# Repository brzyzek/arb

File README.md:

# arb
An arbitrary waveform generator.

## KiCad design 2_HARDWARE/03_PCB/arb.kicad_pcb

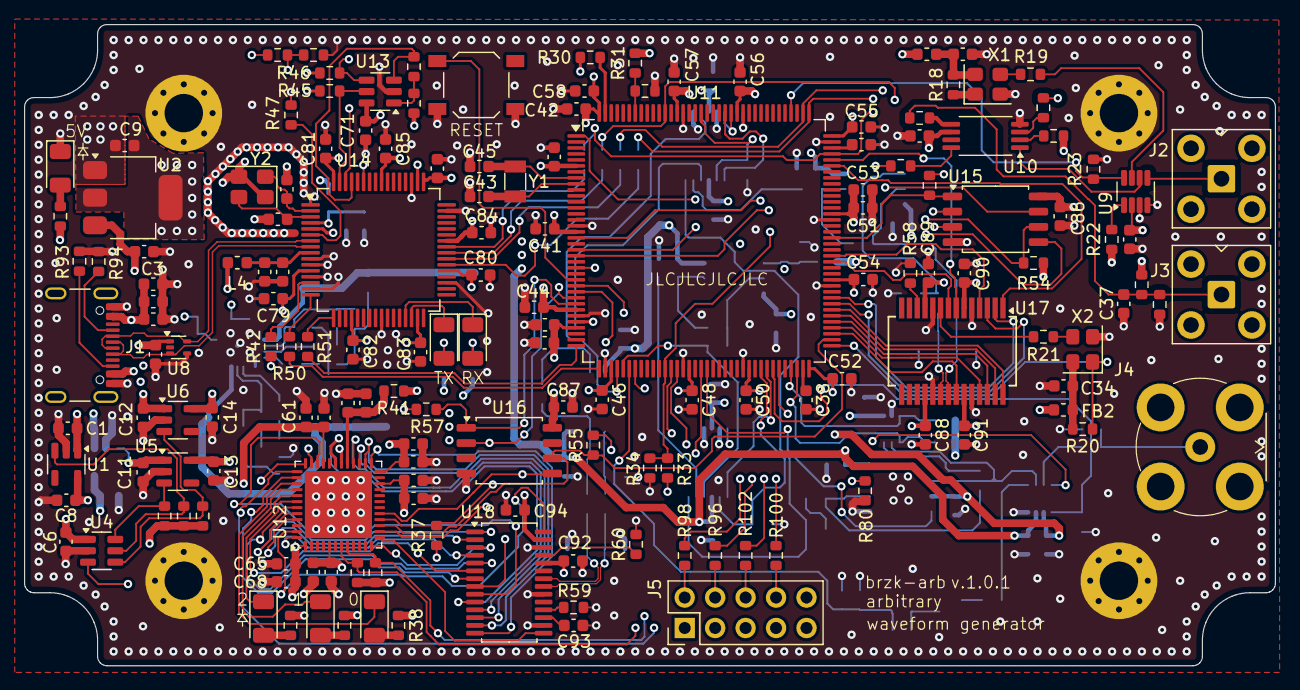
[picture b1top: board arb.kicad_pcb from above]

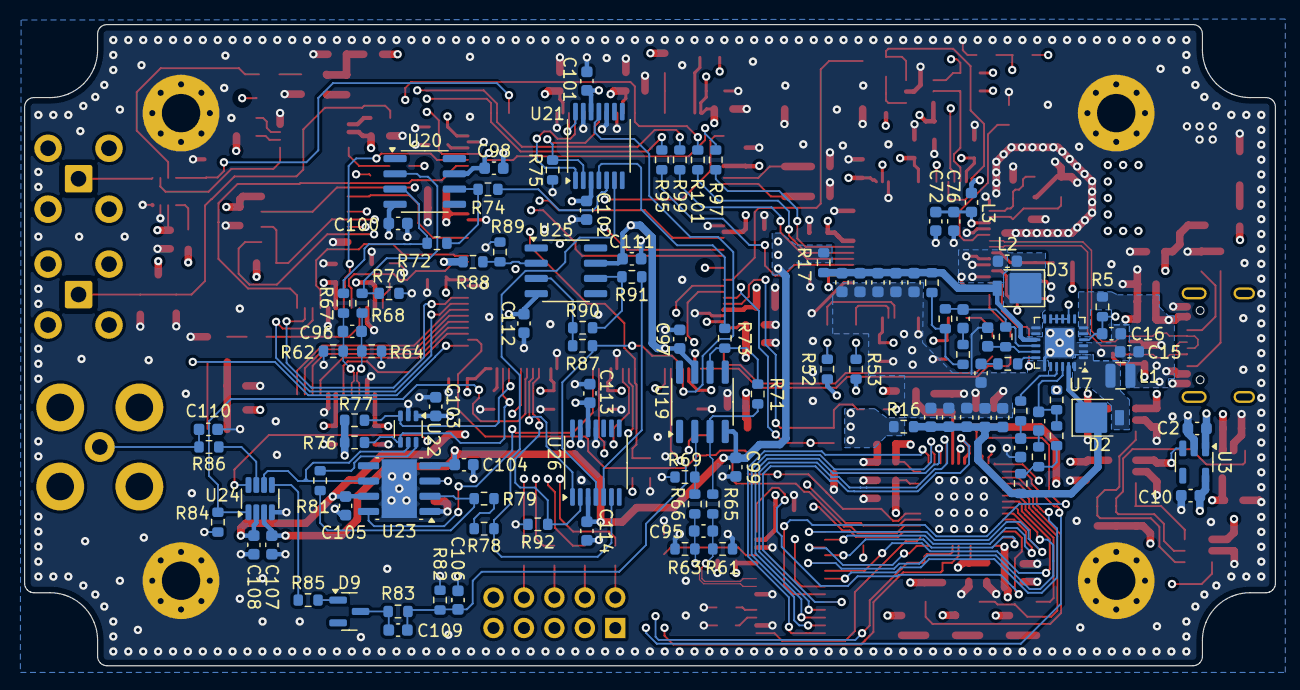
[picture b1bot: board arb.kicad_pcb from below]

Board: 6 copper layers, 104.3 x 53.5 mm, 271 parts (107 on the bottom side), 184 nets.

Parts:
C1, C2, C3, C7, C11, C12, C49, C53: 1u; C_0603_1608Metric
C4, C42: 10u; C_0603_1608Metric
C5, C15, C22, C23, C24, C25, C26, C27, C29, C30, C61, C62, C63, C68, C69, C70, C72, C74: 4.7u; C_0603_1608Metric
C6, C16, C28, C31, C32, C33, C34, C35, C36, C40, C41, C44, C46, C47, C48, C50, C51, C52, C54, C55, C56, C57, C58, C59, C60, C64, C65, C66, C67, C71, C76, C78, C79, C80, C81, C82, C83, C84, C85, C86, C87, C88, C89, C90, C91, C92, C93, C94, C97, C98, C99, C100, C101, C102, C103, C104, C105, C107, C108, C111, C112, C113, C114: 100n; C_0603_1608Metric
C8, C9, C10, C13, C14, C38, C39: 2.2u; C_0603_1608Metric
C17: 10n; C_0603_1608Metric
C18: 4.7n; C_0603_1608Metric
C19, C21: 6.8p; C_0603_1608Metric
C20: 220n; C_0603_1608Metric
C37, C95, C96, C106, C109: 5p; C_0603_1608Metric
C43, C45: 15p; C_0603_1608Metric
C73, C75: 27p; C_0603_1608Metric
C77: 3.3u; C_0603_1608Metric
C110: 22p; C_0603_1608Metric
D1, D4, D5, D6, D7, D8: LED; LED_1206_3216Metric
D2, D3: MBRM120ET1G; D_SMP_DO-216AA
D9: BAT54L; SOT-23
FB1: 100@100MHz; L_0603_1608Metric
FB2: 30@100MHz; L_0603_1608Metric
H1, H2, H3, H4: MOUNTING HOLE; MountingHole_3.2mm_M3_Pad_Via
J1: TYPE-C-31-M-12; USB_C_Receptacle_GCT_USB4105-xx-A_16P_TopMnt_Horizontal
J2, J3: SMA; SMA_TH_Horizontal_KH-SMA-K513-G
J4: BNC; BNC_TH_Horizontal_DOSIN-801-0050
J5: PH-00244; PinHeader_2x05_P2.54mm_Vertical
L1: 4.7u; L_SMD_L2.5_W2.0_Metric
L2: 4.7u; L_0603_1608Metric
L3, L4: 10u; L_0603_1608Metric
R1, R2, R3, R18, R20, R22, R23, R24, R30, R31, R32, R33, R34, R35, R36, R37, R43, R45, R46, R49, R54, R55, R56, R57, R60, R75, R84, R92: 10k; R_0603_1608Metric
R4, R69, R71, R87, R88, R89, R90: 499; R_0603_1608Metric
R5, R25, R26, R41: 100; R_0603_1608Metric
R6, R7, R10, R11, R14, R15, R16, R17, R29, R50, R51, R73, R74, R78, R79, R80, R81, R82, R85, R91, R95, R96, R97, R98, R99, R100, R101, R102: 0; R_0603_1608Metric
R8: 976k; R_0603_1608Metric
R9: 84.5k; R_0603_1608Metric
R12: 104k; R_0603_1608Metric
R13: 1.30M; R_0603_1608Metric
R19, R21, R27, R28, R61, R62, R63, R64: 24.9; R_0603_1608Metric
R38, R39, R40, R52, R53: 220; R_0603_1608Metric
R42, R70, R72: 1k; R_0603_1608Metric
R44: 2.05k; R_0603_1608Metric
R47: 12k; R_0603_1608Metric
R48, R76, R77: 4.7k; R_0603_1608Metric
R58: 3.9k; R_0603_1608Metric
R59: 2k; R_0603_1608Metric
R65, R66, R67, R68: 226; R_0603_1608Metric
R83: 124k; R_0603_1608Metric
R86: 50; R_0603_1608Metric
R93, R94: 5.1k; R_0603_1608Metric
SW1: TS-1187A-B-A-B; SW_SPST_BUTTON_TS-1187A-B-A-B
U1, U3: TLV70333DBV; SOT-23-5
U2: TLV76133DCY; SOT-223-3_TabPin2
U4: LM3880MF-1AA; SOT-23-6
U5: TLV70312DBV; SOT-23-5
U6: TLV70325DBV; SOT-23-5
U7: TPS65131RGE; VQFN-24-1EP_4x4mm_P0.5mm_EP2.45x2.45mm
U8: TPD2E001DRL; SOT-553
U9, U24: ADG1219BRJZ; SOT-23-8
U10: LMK1C1103PWR; TSSOP-8_4.4x3mm_P0.65mm
U11: STM32F446ZETx; LQFP-144_20x20mm_P0.5mm
U12: ICE40UP5K-SG48ITR; QFN-48-1EP_7x7mm_P0.5mm_EP5.6x5.6mm
U13: 93LC56BT-I_OT; SOT-23-6
U14: FT2232HL; LQFP-64_10x10mm_P0.5mm
U15, U16: W25Q128JVSIQ; SOIC-8_5.3x5.3mm_P1.27mm
U17: AD9850; SSOP-28_5.3x10.2mm_P0.65mm
U18: AD9744; TSSOP-28_4.4x9.7mm_P0.65mm
U19, U20, U25: LM6171; SOIC-8_3.9x4.9mm_P1.27mm
U21, U26: TMUX6104; TSSOP-14_4.4x5mm_P0.65mm
U22: TPL0401B-10; Texas_R-PDSO-G6
U23: THS3491; Texas_R-PDSO-G8_EP2.95x4.9mm_Mask2.4x3.1mm
X1: ASE-10.000MHz; Oscillator_SMD_Abracon_ASE-4Pin_3.2x2.5mm
X2: ASE-100.000MHz; Oscillator_SMD_Abracon_ASE-4Pin_3.2x2.5mm
Y1: 32.768k; Crystal_SMD_3215-2Pin_3.2x1.5mm
Y2: 12 MHz; Crystal_SMD_3225-4Pin_3.2x2.5mm

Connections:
1P2V_D: C13.1, C66.1, C69.1, R41.1, U5.5 (OUT), U12.5 (VCC), U12.30 (VCC)
1P8V_D: C77.1, C79.1, C80.1, C81.1, U14.12 (VCORE), U14.37 (VCORE), U14.49 (VREGOUT), U14.64 (VCORE)
2P5V_D: C14.1, C63.1, C64.1, U6.5 (OUT), U12.24 (VPP_2V5)
3P3V_A: C10.1, C47.1, C49.1, C88.1, C89.1, C92.1, C103.1, R88.1, U3.5 (OUT), U11.33 (VDDA), U17.11 (AVDD), U17.18 (AVDD), U18.24 (AVDD), U22.1 (VDD)
3P3V_D: C9.1, C35.1, C36.1, C40.1, C41.1, C42.1, C44.1, C46.1, C48.1, C50.1, C51.1, C52.1, C53.1, C54.1, C55.1, C56.1, C57.1, C58.1, C71.1, C82.1, C83.1, C84.1, C85.1, C86.1, C87.1, C90.1, C91.1, C94.1, FB1.1, FB2.1, J5.1, L3.1, L4.1, R1.2, R2.2, R3.2, R22.2, R24.2, R25.2, R30.1, R31.2, R33.1, R38.1, R39.1, R40.1, R42.1, R43.1, R45.1, R46.1, R52.1, R53.1, R54.2, R55.2, R56.2, R57.2, R76.2, R77.2, U2.2 (VO), U4.3 (EN), U9.2 (VDD), U10.6 (VDD), U11.6 (VBAT), U11.17 (VDD), U11.30 (VDD), U11.32 (VREF+), U11.39 (VDD), U11.52 (VDD), U11.62 (VDD), U11.72 (VDD), U11.84 (VDD), U11.95 (VDDUSB), U11.108 (VDD), U11.121 (VDD), U11.131 (VDD), U11.144 (VDD), U13.6 (VCC), U14.20 (VCCIO), U14.31 (VCCIO), U14.42 (VCCIO), U14.50 (VREGIN), U14.56 (VCCIO), U15.8 (VCC), U16.8 (VCC), U17.6 (DVDD), U17.23 (DVDD), U18.27 (DVDD)
3P3V_D_FPGA: C8.1, C59.1, C60.1, C61.1, C62.1, C65.1, C68.1, R35.2, R36.2, R37.2, U1.5 (OUT), U12.1 (VCCIO_2), U12.22 (SPI_VCCIO1), U12.33 (VCCIO_0)
5P0V: C1.1, C2.1, C3.1, C4.1, C5.1, C6.1, C7.1, C11.1, C12.1, C15.1, C28.1, J1.A4 (VBUS), J1.A9 (VBUS), J1.B4 (VBUS), J1.B9 (VBUS), L1.1, R4.2, R5.1, R48.1, U1.1 (IN), U2.3 (VI), U3.1 (IN), U3.3 (EN), U4.1 (VCC), U5.1 (IN), U6.1 (IN), U7.5 (INN), U7.6 (INN), U8.1 (VCC)
15P0V_A: C97.1, C98.1, C101.1, C105.1, C108.1, C111.1, C113.1, R16.1, U19.7 (V+), U20.7 (V+), U21.12 (VDD), U23.7 (V+), U24.2 (VDD), U25.7 (V+), U26.12 (VDD)
ANALOG_CAL-ADC_AMUX2_MCU: C106.2, C109.1, R82.1, R83.2, U11.42 (PA6)
ANALOG_DAC1_MCU_AMUX1: U11.40 (PA4), U21.11 (S3)
ANALOG_DAC2_MCU_AMUX3: R87.2, U11.41 (PA5), U26.4 (S1)
ANALOG_DC-OFFSET_AMUX3_AMP3: R78.1, U21.6 (D), U26.6 (D)
ANALOG_DDS_AMP2_AMUX1: R74.2, U21.5 (S2)
ANALOG_DDS_OUT_N: C96.2, R64.2, R68.1, U17.20 (IOUTB)
ANALOG_DDS_OUT_P: C96.1, R62.2, R67.1, U17.21 (IOUT)
ANALOG_FPGA-DAC_AMP1_AMUX1: R73.2, U21.4 (S1)
ANALOG_FPGA-DAC_OUT_N: C95.2, R63.2, R66.1, U18.21 (IOUTB)
ANALOG_FPGA-DAC_OUT_P: C95.1, R61.2, R65.1, U18.22 (IOUTA)
ANALOG_STAGE-2_AMUX2_EXT: C110.2, J4.1 (In), R86.1
CLK_10MHZ_DIST_EXT_3P3: C37.2, J3.1 (In), R25.1, R26.2, R29.1
CLK_10MHZ_DIST_FPGA_3P3: R28.1, U12.35 (IOT_46b_G0)
CLK_10MHZ_DIST_MCU_3P3: R27.1, U11.23 (PH0)
CLK_10MHZ_EXT_SW_3P3: J2.1 (In), U9.5 (SB)
CLK_100MHZ_DDS_3P3: R21.1, U17.9 (CLKIN)
GND: C1.2, C2.2, C3.2, C4.2, C5.2, C6.2, C7.2, C8.2, C9.2, C10.2, C11.2, C12.2, C13.2, C14.2, C15.2, C16.2, C17.2, C18.2, C20.2, C22.2, C23.2, C24.2, C25.2, C26.2, C27.2, C28.2, C29.2, C30.2, C31.2, C32.2, C33.2, C34.2, C35.2, C36.2, C37.1, C38.2, C39.2, C40.2, C41.2, C42.2, C43.2, C44.2, C45.2, C46.2, C47.2, C48.2, C49.2, C50.2, C51.2, C52.2, C53.2, C54.2, C55.2, C56.2, C57.2, C58.2, C59.2, C60.2, C61.2, C62.2, C63.2, C64.2, C65.2, C66.2, C67.2, C68.2, C69.2, C70.2, C71.2, C72.2, C73.2, C74.2, C75.2, C76.2, C77.2, C78.2, C79.2, C80.2, C81.2, C82.2, C83.2, C84.2, C85.2, C86.2, C87.2, C88.2, C89.2, C90.2, C91.2, C92.2, C93.2, C94.2, C97.2, C98.2, C99.2, C100.2, C101.2, C102.2, C103.2, C104.2, C105.2, C106.1, C107.2, C108.2, C110.1, C111.2, C112.2, C113.2, C114.2, D1.1 (K), H1.1, H2.1, H3.1, H4.1, J1.A1 (GND), J1.A12 (GND), J1.B1 (GND), J1.B12 (GND), J1.S1 (SHIELD), J2.2 (Ext), J3.2 (Ext), J4.2 (Ext), J5.3, J5.5, J5.7, J5.9, L2.1, R9.2, R23.1, R26.1, R32.2, R34.1, R47.2, R49.2, R58.2, R59.2, R60.2, R61.1, R62.1, R63.1, R64.1, R69.1, R70.1, R75.1, R80.1, R82.2, R84.1, R89.1, R92.1, R93.1, R94.1, SW1.C1 (NO_1), SW1.D1 (NO_2), U1.2 (GND), U2.1 (GND), U3.2 (GND), U4.2 (GND), U5.2 (GND), U6.2 (GND), U7.2 (PGND), U7.3 (PGND), U7.19 (AGND), U7.25 (EP), U8.4 (GND), U9.3 (GND), U9.4 (VSS), U10.4 (GND), U11.16 (VSS), U11.31 (VSSA), U11.38 (VSS), U11.51 (VSS), U11.61 (VSS), U11.83 (VSS), U11.94 (VSS), U11.107 (VSS), U11.120 (VSS), U11.130 (VSS), U12.49 (GND), U13.2 (VSS), U14.1 (GND), U14.5 (GND), U14.10 (AGND), U14.11 (GND), U14.13 (TEST), U14.15 (GND), U14.25 (GND), U14.35 (GND), U14.47 (GND), U14.51 (GND), U15.4 (GND), U16.4 (GND), U17.5 (DGND), U17.10 (AGND), U17.19 (AGND), U17.24 (DGND), U18.16 (REFLO), U18.20 (AGND), U18.26 (DGND), U21.10 (S4), U21.13 (GND), U22.2 (GND), U23.1 (REF), U23.9 (EP), U24.4 (VSS), U26.11 (S3), U26.13 (GND), X1.2 (GND), X2.2 (GND), Y2.2, Y2.4
GPIO_1P2-EN_SEQ_REG_3P3: R1.1, U4.6 (FLAG1), U5.3 (EN)
GPIO_2P5-EN_SEQ_REG_3P3: R3.1, U4.4 (FLAG3), U6.3 (EN)
GPIO_3P3-EN_SEQ_REG_3P3: R2.1, U1.3 (EN), U4.5 (FLAG2)
GPIO_100M-EN_MCU_100M-OSC_3P3: R20.1, U11.73 (PB12), X2.1 (EN)
GPIO_AMP-PD_MCU_AMP2_3P3: U11.55 (PF15), U23.8 (~PD)
GPIO_BOOT0_SW_MCU_3P3_L: R31.1, R32.1, U11.138 (BOOT0)
GPIO_BOOT1_SW_MCU_3P3_L: R33.2, R34.2, R54.1, U11.48 (PB2), U15.6 (CLK)
GPIO_CFG_DONE_FPGA_MCU_3P3: R35.1, U11.49 (PF11), U12.7 (CDONE)
GPIO_CLK_EN_MCU_FPGA_3P3: U11.54 (PF14), U12.37 (IOT_45a_G1)
GPIO_D0_MCU_DDS_3P3: U11.88 (PG3), U17.4 (D0)
GPIO_D1_MCU_DDS_3P3: U11.80 (PD11), U17.3 (D1)
GPIO_D2_MCU_DDS_3P3: U11.81 (PD12), U17.2 (D2)
GPIO_D3_MCU_DDS_3P3: U11.103 (PA11), U17.1 (D3)
GPIO_D4_MCU_DDS_3P3: U11.79 (PD10), U17.28 (D4)
GPIO_D5_MCU_DDS_3P3: U11.78 (PD9), U17.27 (D5)
GPIO_D6_MCU_DDS_3P3: U11.77 (PD8), U17.26 (D6)
GPIO_D7_MCU_DDS_3P3: U11.76 (PB15), U17.25 (D7)
GPIO_DACB0_FPGA_DAC_3P3: U12.25 (IOT_36b), U18.14 (D0)
GPIO_DACB1_FPGA_DAC_3P3: U12.26 (IOT_39a), U18.13 (D1)
GPIO_DACB2_FPGA_DAC_3P3: U12.27 (IOT_38b), U18.12 (D2)
GPIO_DACB3_FPGA_DAC_3P3: U12.28 (IOT_41a), U18.11 (D3)
GPIO_DACB4_FPGA_DAC_3P3: U12.31 (IOT_42b), U18.10 (D4)
GPIO_DACB5_FPGA_DAC_3P3: U12.34 (IOT_44b), U18.9 (D5)
GPIO_DACB6_FPGA_DAC_3P3: U12.36 (IOT_48b), U18.8 (D6)
GPIO_DACB7_FPGA_DAC_3P3: U12.38 (IOT_50b), U18.7 (D7)
GPIO_DACB8_FPGA_DAC_3P3: U12.42 (IOT_51a), U18.6 (D8)
GPIO_DACB9_FPGA_DAC_3P3: U12.43 (IOT_49a), U18.5 (D9)
GPIO_DACB10_FPGA_DAC_3P3: U12.48 (IOB_4a), U18.4 (D10)
GPIO_DACB11_FPGA_DAC_3P3: U12.12 (IOB_22a), U18.3 (D11)
GPIO_DACB12_FPGA_DAC_3P3: U12.45 (IOB_5b), U18.2 (D12)
GPIO_DACB13_FPGA_DAC_3P3: U12.44 (IOB_3b_G6), U18.1 (D13)
GPIO_DACCLK_FPGA_DAC_3P3: U12.47 (IOB_2a), U18.28 (CLK)
GPIO_DACSLEEP_FPGA_DAC_3P3: U12.13 (IOB_24a), U18.15 (SLEEP)
GPIO_EN_MCU_AMUX1_3P3: R75.2, U11.127 (PG12), U21.2 (EN)
GPIO_EN_MCU_AMUX2_3P3: R84.2, U11.66 (PE13), U24.1 (EN)
GPIO_EN_MCU_AMUX3_3P3: R92.2, U11.64 (PE11), U26.2 (EN)
GPIO_FPGARST_MCU_FPGA_3P3_L: R36.1, U11.50 (PF12), U12.8 (~CRESET)
GPIO_FQ-UD_MCU_DDS_3P3: U11.87 (PG2), U17.8 (FQ_UD)
GPIO_LED0_FPGA_LED_OD: D4.1 (K), U12.39 (RGB0)
GPIO_LED1_FPGA_LED_OD: D5.1 (K), U12.40 (RGB1)
GPIO_LED2_FPGA_LED_OD: D6.1 (K), U12.41 (RGB2)
GPIO_RST_MCU_3P3_L: SW1.A1 (COM_1), U11.25 (NRST)
GPIO_RST_MCU_DDS_3P3: U11.75 (PB14), U17.22 (RESET)
GPIO_SEL0_MCU_AMUX1_3P3: U11.123 (PD7), U21.1 (A0)
GPIO_SEL0_MCU_AMUX3_3P3: U11.65 (PE12), U26.1 (A0)
GPIO_SEL1_MCU_AMUX1_3P3: U11.122 (PD6), U21.14 (A1)
GPIO_SEL1_MCU_AMUX3_3P3: U11.43 (PA7), U26.14 (A1)
GPIO_SEL_MCU_AMUX2_3P3: U11.67 (PE14), U24.8 (IN)
GPIO_SW-SEL_MCU_CLKMUX_3P3: R23.2, U9.8 (IN), U11.112 (PC11)
GPIO_UART_RXLED_FTDI_L: D7.1 (K), U14.29 (ACBUS3)
GPIO_UART_TXLED_FTDI_L: D8.1 (K), U14.30 (ACBUS4)
GPIO_W-CLK_MCU_DDS_3P3: U11.104 (PA12), U17.7 (W_CLK)
I2C_SCL_MCU_POT_3P3: R77.1, U11.69 (PB10), U22.3 (SCL)
I2C_SDA_MCU_POT_3P3: R76.1, U11.70 (PB11), U22.4 (SDA)
JTAG_CON_TCK_3P3: J5.4, R96.2
JTAG_CON_TDI_3P3: J5.8, R100.2
JTAG_CON_TDO_3P3: J5.6, R102.2
JTAG_CON_TMS_3P3: J5.2, R98.2
JTAG_FTDI_TCK_3P3: R95.2, U14.38 (BDBUS0)
JTAG_FTDI_TDI_3P3: R99.2, U14.39 (BDBUS1)
JTAG_FTDI_TDO_3P3: R101.2, U14.40 (BDBUS2)
JTAG_FTDI_TMS_3P3: R97.2, U14.41 (BDBUS3)
JTAG_MCU_TCK_3P3: R95.1, R96.1, U11.109 (PA14)
JTAG_MCU_TDI_3P3: R99.1, R100.1, U11.110 (PA15)
JTAG_MCU_TDO_3P3: R101.1, R102.1, U11.133 (PB3)
JTAG_MCU_TMS_3P3: R97.1, R98.1, U11.105 (PA13)
N15P0V_A: C99.1, C100.1, C102.1, C104.1, C107.1, C112.1, C114.1, R17.1, U19.4 (V-), U20.4 (V-), U21.3 (VSS), U23.4 (V-), U24.3 (GND), U25.4 (V-), U26.3 (VSS)
unnamed: C17.1, R6.2
unnamed: C18.1, R10.2
unnamed: C19.1, R11.2
unnamed: C21.2, R14.1
unnamed: D1.2 (A), R4.1
unnamed: D2.2 (A), L1.2, U7.1 (INP), U7.24 (INP)
unnamed: C22.1, C24.1, C26.1, C29.1, C31.1, D2.1 (K), R7.1, R16.2, U7.23 (VPOS)
unnamed: C23.1, C25.1, C27.1, C30.1, C32.1, D3.2 (A), R15.2, R17.2, U7.15 (VNEG)
unnamed: D3.1 (K), L2.2, U7.13 (OUTN), U7.14 (OUTN)
unnamed: D4.2 (A), R38.2
unnamed: D5.2 (A), R39.2
unnamed: D6.2 (A), R40.2
unnamed: D7.2 (A), R52.2
unnamed: D8.2 (A), R53.2
unnamed: D9.1 (A), R85.2
unnamed: C109.2, D9.3 (K), R83.1
unnamed: J1.A5 (CC1), R94.2
unnamed: J1.B5 (CC2), R93.2
unnamed: R7.2, R8.1, R11.1
unnamed: R13.2, R14.2, R15.1
unnamed: R71.2, R73.1, U19.6
unnamed: R72.2, R74.1, U20.6
unnamed: R78.2, R79.1
unnamed: R90.2, R91.1, U25.6
unnamed: R10.1, U7.18 (CN)
unnamed: R6.1, U7.21 (CP)
unnamed: C16.1, R5.2, U7.4 (VIN), U7.8 (ENP), U7.9 (PSP), U7.10 (ENN), U7.11 (PSN)
unnamed: C21.1, R12.2, R13.1, U7.16 (FBN)
unnamed: C19.2, R8.2, R9.1, U7.22 (FBP)
unnamed: C20.1, R12.1, U7.17 (VREF)
unnamed: R22.1, U9.1 (EN)
unnamed: R19.1, U9.7 (SA)
unnamed: R24.1, U10.2 (1G)
unnamed: U9.6 (D), U10.1 (CLKIN)
unnamed: R27.2, U10.3 (Y0)
unnamed: R28.2, U10.8 (Y1)
unnamed: R29.2, U10.5 (Y2)
unnamed: C45.1, U11.8 (PC14), Y1.2
unnamed: C43.1, U11.9 (PC15), Y1.1
unnamed: R30.2, U11.143 (PDR_ON)
unnamed: C38.1, U11.71 (VCAP_1)
unnamed: C39.1, U11.106 (VCAP_2)
unnamed: C67.1, C70.1, R41.2, U12.29 (VCCPLL)
unnamed: R46.2, U13.4 (CLK), U14.62 (EECLK)
unnamed: R45.2, U13.5 (CS), U14.63 (EECS)
unnamed: R44.1, U13.3 (DI), U14.61 (EEDATA)
unnamed: R43.2, R44.2, U13.1 (DO)
unnamed: R50.1, U14.16 (ADBUS0)
unnamed: R51.1, U14.17 (ADBUS1)
unnamed: R48.2, R49.1, U14.59 (BCBUS7)
unnamed: C73.1, U14.2 (OSCI), Y2.1
unnamed: C75.1, U14.3 (OSCO), Y2.3
unnamed: R47.1, U14.6 (REF)
unnamed: C72.1, C76.1, L3.2, U14.4 (VPHY)
unnamed: C74.1, C78.1, L4.2, U14.9 (VPLL)
unnamed: R42.2, U14.14 (~RESET)
unnamed: R58.1, U17.12 (RSET)
unnamed: R59.1, U18.18 (FS_ADJ)
unnamed: R60.1, U18.25 (MODE)
unnamed: C93.1, U18.17 (REFIO)
unnamed: R65.2, R71.1, U19.3 (+)
unnamed: R66.2, R69.2, U19.2 (-)
unnamed: R67.2, R72.1, U20.3 (+)
unnamed: R68.2, R70.2, U20.2 (-)
unnamed: R81.1, U22.6 (H)
unnamed: U22.5 (W), U23.6, U24.6 (D)
unnamed: R80.2, U23.3 (+)
unnamed: R79.2, R81.2, U23.2 (-)
unnamed: R86.2, U24.7 (SA)
unnamed: R85.1, U24.5 (SB)
unnamed: R87.1, R90.1, U25.3 (+)
unnamed: R88.2, R89.2, U25.2 (-)
unnamed: R91.2, U26.5 (S2)
unnamed: R18.1, X1.1 (EN)
unnamed: R19.2, X1.3 (OUT)
unnamed: C33.1, FB1.2, R18.2, X1.4 (Vdd)
unnamed: R21.2, X2.3 (OUT)
unnamed: C34.1, FB2.2, R20.2, X2.4 (Vdd)
QSPI_IO0_MCU_FLASH_3P3: U11.20 (PF8), U15.5 (DI(IO0))
QSPI_IO1_MCU_FLASH_3P3: U11.21 (PF9), U15.2 (DO(IO1))
QSPI_IO2_MCU_FLASH_3P3: U11.1 (PE2), U15.3 (IO2)
QSPI_IO3_MCU_FLASH_3P3: U11.18 (PF6), U15.7 (IO3)
QSPI_NCS_MCU_FLASH_3P3: R56.1, U11.91 (PG6), U15.1 (~CS)
SPI_CS_MCU_FLASH_3P3_L: R57.1, U11.29 (PC3), U16.1 (~CS)
SPI_CS_MCU_FPGA_3P3_L: R37.1, U11.26 (PC0), U12.16 (IOB_35b_SPI_SS)
SPI_MISO_FPGA_MCU_3P3: U11.28 (PC2), U12.14 (IOB_32a_SPI_SO), U16.2 (DO(IO1))
SPI_MOSI_MCU_FPGA_3P3: U11.27 (PC1), U12.17 (IOB_33b_SPI_SI), U16.5 (DI(IO0))
SPI_SCLK_MCU_FPGA_3P3: R55.1, U11.74 (PB13), U12.15 (IOB_34a_SPI_SCK), U16.6 (CLK)
UART_FTDITX_MCURX_3P3: R50.2, U11.37 (PA3)
UART_MCUTX_FTDIRX_3P3: R51.2, U11.36 (PA2)
USB_DATA_CONN_FTDI_N: J1.A7 (D-), J1.B7 (D-), U8.5 (D-), U14.7 (DM)
USB_DATA_CONN_FTDI_P: J1.A6 (D+), J1.B6 (D+), U8.3 (D+), U14.8 (DP)

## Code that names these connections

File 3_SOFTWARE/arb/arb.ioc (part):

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Mcu.Name=STM32F446Z(C-E)Tx
Mcu.Package=LQFP144
Mcu.UserName=STM32F446ZETx
PA11.Signal=GPIO_Output
PA12.Signal=GPIO_Output
PA13.Mode=JTAG_4_pins
PA13.Signal=SYS_JTMS-SWDIO
PA14.Mode=JTAG_4_pins
PA14.Signal=SYS_JTCK-SWCLK
PA15.Mode=JTAG_4_pins
PA15.Signal=SYS_JTDI
PA2.Mode=Asynchronous
PA2.Signal=USART2_TX
PA3.Mode=Asynchronous
PA3.Signal=USART2_RX
PA4.Signal=COMP_DAC1_group
PA5.Signal=COMP_DAC2_group
PA6.Signal=ADCx_IN6
PA7.Signal=GPIO_Output
PB10.Mode=I2C
PB10.Signal=I2C2_SCL
PB11.Mode=I2C
PB11.Signal=I2C2_SDA
PB12.Signal=GPIO_Output
PB13.Mode=Full_Duplex_Master
PB13.Signal=SPI2_SCK
PB14.Signal=GPIO_Output
PB15.Signal=GPIO_Output
PB2.Mode=Single Bank 1
PB2.Signal=QUADSPI_CLK
PB3.Mode=JTAG_4_pins
PB3.Signal=SYS_JTDO-SWO
PC0.Signal=GPIO_Output
PC1.Mode=Full_Duplex_Master
PC1.Signal=SPI2_MOSI
PC11.Signal=GPIO_Output
PC14-OSC32_IN.Signal=RCC_OSC32_IN
PC15-OSC32_OUT.Signal=RCC_OSC32_OUT
PC2.Mode=Full_Duplex_Master
PC2.Signal=SPI2_MISO
PC3.Signal=GPIO_Output
PD10.Signal=GPIO_Output
PD11.Signal=GPIO_Output
PD12.Signal=GPIO_Output
PD6.Signal=GPIO_Output
PD7.Signal=GPIO_Output
PD8.Signal=GPIO_Output
PD9.Signal=GPIO_Output
PE11.Signal=GPIO_Output
PE12.Signal=GPIO_Output
PE13.Signal=GPIO_Output
PE14.Signal=GPIO_Output
PE2.Mode=Single Bank 1
PE2.Signal=QUADSPI_BK1_IO2
PF11.Signal=GPIO_Input
PF12.Signal=GPIO_Output
PF14.Signal=GPIO_Output
PF15.Signal=GPIO_Output
PF6.Mode=Single Bank 1
PF6.Signal=QUADSPI_BK1_IO3
PF8.Mode=Single Bank 1
PF8.Signal=QUADSPI_BK1_IO0
PF9.Mode=Single Bank 1
PF9.Signal=QUADSPI_BK1_IO1
PG12.Signal=GPIO_Output
PG2.Signal=GPIO_Output
PG3.Signal=GPIO_Output
PG6.Mode=Single Bank 1
PG6.Signal=QUADSPI_BK1_NCS
PH0-OSC_IN.Signal=RCC_OSC_IN
board=custom

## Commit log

2024-09-01 SETUP
2024-09-01 FEAT: Created Initial block diagram.
2024-09-02 FEAT: Modified Block Diagram. Simplified to a DDS Design.
2024-09-03 FEAT: Modified Block Diagram /w new Layout (& FPGA), added BOM Template.
2024-09-03 MINOR: Removed .directory file.
2024-09-08 FEAT: Modified Block Diagram, added FPGA, DDS, and P/Ns.
2024-09-12 MINOR: Setup KiCAD Template.
2024-09-12 MINOR: Added KiCAD Custom Symbol and Footprint Pointers.
2024-09-12 MINOR: Removing .directory and .bkp files.
2024-09-16 FEAT: Modified Block Diagram. Added Pin Map Excel.
2024-09-17 FEAT: Added Level Translator Sheet, Symbols, added DAC and DDS to Schematic.
2024-09-22 FEAT: Finished Excel Pin Map for FPGA.
2024-09-28 FEAT: Finished Excel Pin Map for MCU. Completed MCU + FPGA in Schematic.
2024-09-28 FEAT: Added FTDI JTAG. Added 0 Ohm JTAG Resistors. Added Boot Select Switches.
2024-09-30 MINOR: Updated Block Diagram with preliminary post DAC stage analog design.
2024-10-06 FEAT: Added some Amplifier Simulations. Modified Block Diagram Analog Path.
2024-10-12 FEAT: Simulated Analog Paths, added first stage analog amp to schematic.
2024-10-18 FEAT: Added Analog Stage 2 to Schematic. Some additional symbols (Pot, SPDT Analog MUX, etc.) added to Project.
2024-10-19 FEAT: Added RVP Diode + Attenuation on the Cal Path.
2024-10-21 FEAT: Swapped out DDS IC and connected. Started adding Clockign Components into Schematic.
2024-10-27 FEAT: Created Power Consumption Matrix.
2024-10-28 FEAT: Added MCU Resources for Analog Muxing, Additional DAC, ADC, and I2C for Digital Pot. Also changed SPI Resource from 1 to 2.
2024-10-28 FEAT: Changed from two grounds (Digital + Analog) to Singular Ground IAW recommended Grounding Scheme.
2024-10-28 MINOR: Updated Pin Map with new MCU Resources and filled out STM32 .ioc file with GPIO In/Out and all Resources.
2024-11-03 FEAT: Added +15V and -15V Regulator. Replaced some Symbols to add additional Part Number Field.
2024-11-05 FEAT: Added USB ESD Protection.
2024-11-09 FEAT: Added Clocking Sheet, FPGA Flash, and FPGA Decoupling.
2024-11-10 FEAT: Added Connectors on Schematic. Created Connector Footprints.
2024-11-10 FEAT: Assigned Reference Designators; Assigned Passives Part Numbers & Footprints (0603); Assigned LCSC P/Ns.
2024-11-11 FEAT: Added MCU Flash. Finished creating & assigning footprints. Ran ERC & cleared out issues. Ready for Layout.
2024-11-16 MINOR: Verified Footprints to Datasheets. Added Pull Ups on FPGA DONE/Config/SPI Chip Select Pins.
2024-11-17 MINOR: Added Board Rules & Constraints.
2024-11-22 FEAT: Initial board placement started.
2024-11-23 FEAT: Finished placement of components, switches, etc.
2024-11-24 MINOR: Started laying out signal tracks. About 1/4th of the way done. Started on Digital, 3P3V Power, Clocking.
2024-11-26 FEAT: Changed Inductor to higher current. Continued layout. Assigned some Netclasses.
2024-11-27 FEAT: Laid out some more analog. Laid out FPGA and DDC ICs.
2024-11-28 FEAT: Laid out JTAG, Processor QSPI. Length Matched JTAG.
2024-11-30 FEAT: Laid out MCU DDS. Changed some MCU Pins for better routability.
2024-12-01 MINOR: Laid out +/- 15V Regulator. Some Discrete Signals.
2024-12-19 MINOR: Some minor trace adjustments. Ran trace cleanup tool.
2024-12-21 MINOR: Removed all existing Vias and Tracks.
2024-12-21 FEAT: Placed components for Left-Handed Analog Output.
2024-12-22 FEAT: Placed most components for Right-Handed Analog Output.
2024-12-22 FEAT: Added some Power Planes for 3.3V, 5V. Routed 50 Ohm Analog and Differential.
2024-12-23 MINOR: Continuing layout. USB, Some FTDI, etc.
2024-12-28 MINOR: Continuing layout. Laid Out FPGA Power.
2024-12-28 MINOR: Layout. 3.3V Analog Power, FTDI IC. Clocks.
2024-12-29 MINOR: Layout. Grounds. Misc.
2024-12-30 FEAT: Finished with Power and GND Layout.
2024-12-31 MINOR: Layout, JTAG complete.
2025-01-01 MINOR: Layout, I2C Potentiometer, QSPI MCU Memory.
2025-01-01 MINOR: Layout, working on SPI / QSPI. Currently mixed up.
2025-01-01 MINOR: Layout, working on SPI / QSPI. Fixed issues with Schematic.
2025-01-02 FEAT: Finished DDS, MCU Layout.
2025-01-02 MINOR: Removed arb2 ioc.
2025-01-03 FEAT: Started FPGA Layout, 1/2 Complete.
2025-01-04 FEAT: Completed FPGA Layout.
2025-01-04 MINOR: Adjusted Pin Map per new Layout.
2025-01-05 FEAT: Updated STM32 IOC to Match new Pinout.
2025-01-05 FEAT: Removed Chassis GND, completed routing. Needs to be verified.
2025-01-08 FIX: Resolved Edge Cut issue. Resolved all DRC Errors. Updated minimum annular ring from .2mm to 0.15mm.
2025-01-11 MINOR: Changed Via Sizes from 7/3.5mm to 7/3mm.
2025-01-12 FEAT: Fixed Regulator Layouts. Added Stitching Vias around the outside. Started adding stitching Vias throughout the IC.
2025-01-12 Fixed: Added more stitching VIAs. Fixed outline trace conflicts. Resolved DRC Errors.
2025-01-12 FIX: Fixed 100MHz Clock Routing. Added some via guard rings, fixed Clock Trace Routing.
2025-01-12 MINOR: Removed .lck file from commiting (.gitignore) update.
2025-01-19 MINOR: Adjusted 10MHz clock and vias.
2025-02-06 FIX: Refactoring folder structure.
2025-02-08 FEAT: Added silkscreen.
2025-02-13 FEAT: Added datasheets.
2025-04-13 MINOR: Adjusted soldermask and ported Schematic + PCB to Kicad 9.0.
2025-07-16 MINOR: Adjusted Analog Schematic.
2025-07-16 MINOR: Adjusted schematic version.
2025-07-19 MINOR: Initial Reduced Size Analysis, need to make the board larger.
2025-07-19 MINOR: Changed board outline and started component placement.
2025-07-20 MINOR: Changed Boot Select Switches to Pull-Downs / Pull Up DNI and continued layout.
2025-07-27 MINOR: Completed initial placement.
2025-07-29 MINORL: Completed 3.3V Regulator Power Planes. Started on FTDI Clock.
2025-07-30 MINOR: Routed (most of) the clocks.
2025-07-31 MAJOR: Converted PCB from 4 Layer to 6 Layer, updated board stackup, and added new trace constraints. Updated all active traces on PCB to new widths.
2025-08-07 MINOR: Finalized Clock Routing & started on FTDI Chip Routing.
2025-08-09 MINOR: Finalized FTDI Chip Routing.
2025-08-11 MINOR: Added Power and GND Vias on the Top Layer.
2025-08-13 MINOR: Routed Layer 3 Power Planes.
2025-08-24 MINOR: Added missing vias, started on BS Routing.
2025-08-25 MINOR: Adjusted Fill Clearances to 10 mil, continued with +/-15V Regulator Layout. Added First VIA in Pad.
2025-08-26 FEAT: Laid out +/-15V Regulator. Fixed input resistor into +/-15V Regulator Power. Named Power Planes.
2025-09-01 MINOR: Moved Analog Components for easier routing.
2025-09-03 FEAT: Completed Power Planes, GND, and Analog Placement.
2025-09-17 MINOR: Fixed Board Edge Cuts.
2025-09-21 FEAT: Repinned the MCU to better support new layout.
2025-09-21 FEAT: Routed FPGA to MCU SPI Connections.
2025-09-24 FEAT: Routed high speed signals.
2025-09-26 FEAT: Routed FPGA to DDS and FPGA to MCU Signals.
2025-09-27 FEAT: Routed Analog and all Misc Signals. Routing is complete.
2025-09-28 FEAT: Fixed Silkscreen + Resolved all DRC Errors.
2025-10-04 FEAT: Removed Via in Pad from Design + added sitching vias.
2025-10-12 FEAT: Created BOM.
2025-10-13 MINOR: Adjusted Silkscreen.
